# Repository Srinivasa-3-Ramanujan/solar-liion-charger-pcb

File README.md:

# Solar Li-ion Battery Charger PCB

A fully designed PCB for solar-powered Li-ion battery charging with 
hardware protection — designed from scratch in KiCad.

---

## What this does

Takes input from a solar panel and safely charges a Li-ion battery 
with full hardware protection against overcharge, over-discharge, 
and short circuits. All protection logic is handled in hardware — 
no microcontroller involved.

---

## Why hardware protection matters

Li-ion batteries are dangerous if charged incorrectly — overcharging 
above 4.2V or discharging below 2.5V can cause permanent damage or 
fire. This design handles both in hardware, meaning protection is 
always active regardless of software state.

---

## How it works
1. **TP4056** manages the charging profile (constant current → constant voltage → cutoff at 4.2V)
2. **DW01A** monitors battery voltage using two internal comparators — cuts off at 4.28V (overcharge) and 2.5V (over-discharge)
3. **Dual NMOS** acts as a physical gate controlled by DW01A — disconnects battery when protection triggers

---

## Components

| Component | Role |
|---|---|
| TP4056 | Solar Li-ion charger IC |
| DW01A | Battery protection IC |
| Q1, Q2 (NMOS) | Physical disconnect switches |
| R1 (2.4kΩ) | Sets charging current to 500mA |
| R2 (10kΩ) | Disables temperature monitoring |
| R3, R4 (1kΩ) | LED current limiting resistors |
| D1 (RED LED) | Charging indicator |
| D2 (GREEN LED) | Charge complete indicator |
| C1 (100nF) | Input decoupling capacitor |
| R5 (0.1Ω) | Current sense resistor |

---

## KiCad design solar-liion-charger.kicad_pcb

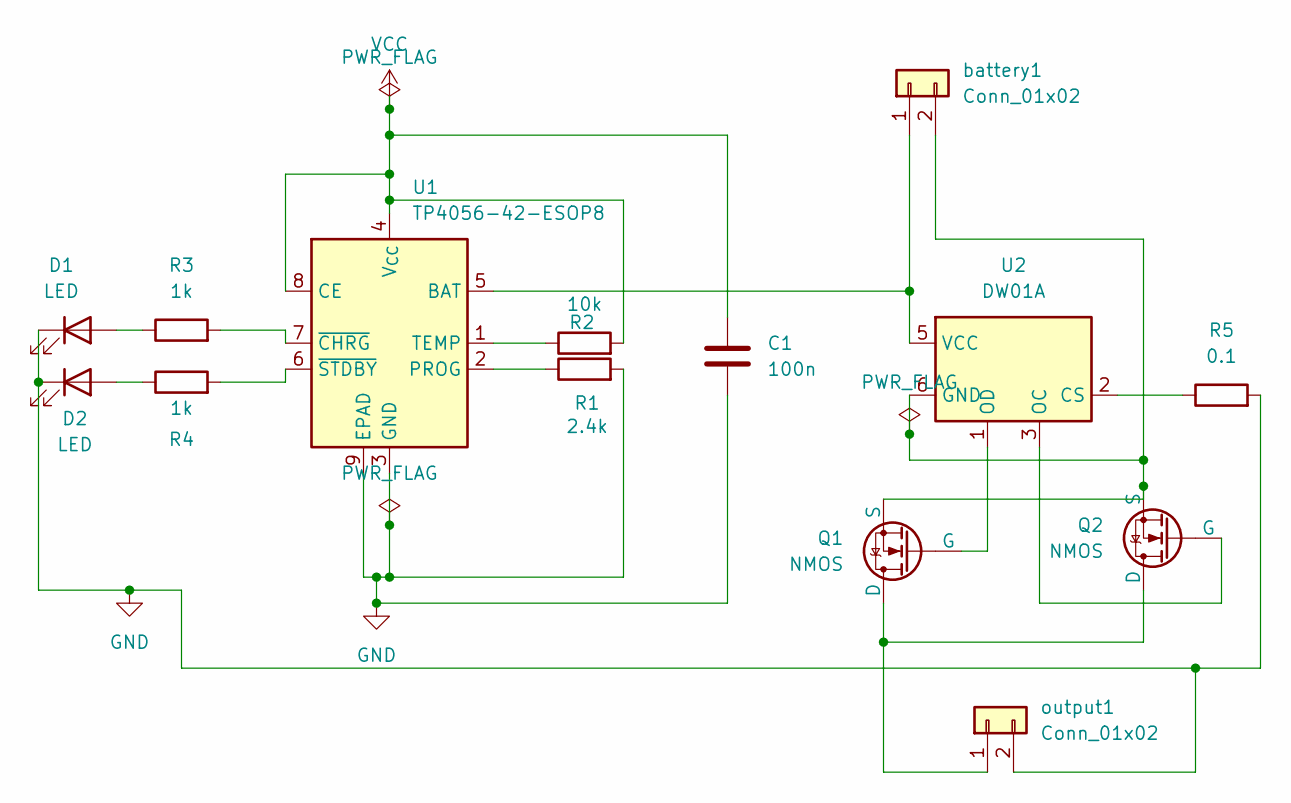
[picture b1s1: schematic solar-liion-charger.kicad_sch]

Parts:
C1: 100n; C_0805_2012Metric
D1, D2: LED; LED_0805_2012Metric
Q1, Q2: NMOS; SOT-23
R1: 2.4k; R_0805_2012Metric
R2: 10k; R_0805_2012Metric
R3, R4: 1k; R_0805_2012Metric
R5: 0.1; R_0805_2012Metric
U1: TP4056-42-ESOP8; SOIC-8-1EP_3.9x4.9mm_P1.27mm_EP2.41x3.3mm_ThermalVias
U2: DW01A; SOT-23-6
battery1: Conn_01x02; PinHeader_1x02_P2.54mm_Vertical
output1: Conn_01x02; PinHeader_1x02_P2.54mm_Vertical

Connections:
GND: C1.2, D1.1 (K), D2.1 (K), R1.2, R5.2, U1.3 (GND), U1.9 (EPAD), output1.2
unnamed: D1.2 (A), R3.1
unnamed: D2.2 (A), R4.1
unnamed: Q1.1 (D), Q2.1 (D), output1.1
unnamed: Q1.2 (G), U2.1 (OD)
unnamed: Q1.3 (S), Q2.3 (S), U2.6 (GND), battery1.2
unnamed: Q2.2 (G), U2.3 (OC)
unnamed: U1.5 (BAT), U2.5 (VCC), battery1.1
unnamed: R1.1, U1.2 (PROG)
unnamed: R2.1, U1.1 (TEMP)
unnamed: R3.2, U1.7 (~CHRG)
unnamed: R4.2, U1.6 (~STDBY)
unnamed: R5.1, U2.2 (CS)
VCC: C1.1, R2.2, U1.4 (V_{CC}), U1.8 (CE)

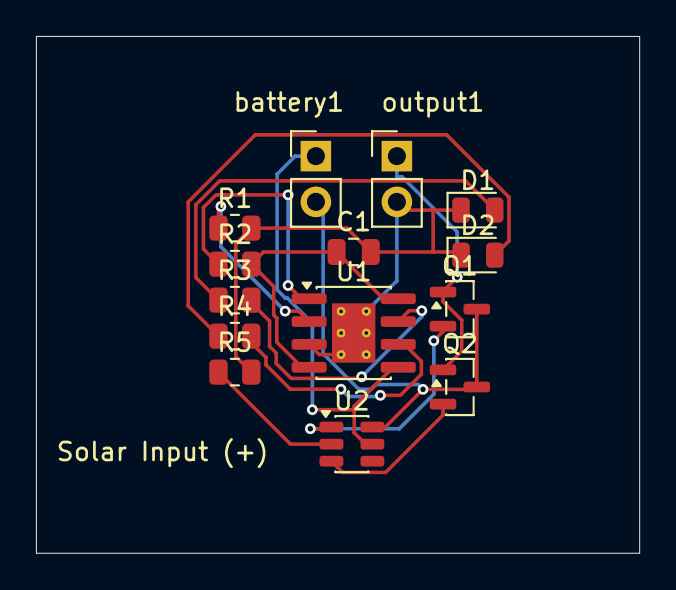
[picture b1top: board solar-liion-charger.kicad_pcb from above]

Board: 2 copper layers, 33.5 x 28.7 mm, 14 parts (0 on the bottom side), 14 nets.

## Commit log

2026-05-25 README.md
2026-05-25 Rename image.png to images/schematic.png
2026-05-25 Rename image.png to 3d-view.png
2026-05-25 Rename image.png to pcb-layout.png
